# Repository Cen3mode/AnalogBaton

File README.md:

TO DO:
	redo GPIO layout,
	redo SD card slot,
	get rid of CAN bus connector (leave broken out on pins),
	redo power from charge pumps to LDOs where possible for simplicity,
	make the board smaller,
	get rid of the cristall (using internal oscillator),
	choose USB-C port with only single row of pins,
	add M3 mounting holes,
	reconfigure charger and fuel gauge,
	add QSPI flash,

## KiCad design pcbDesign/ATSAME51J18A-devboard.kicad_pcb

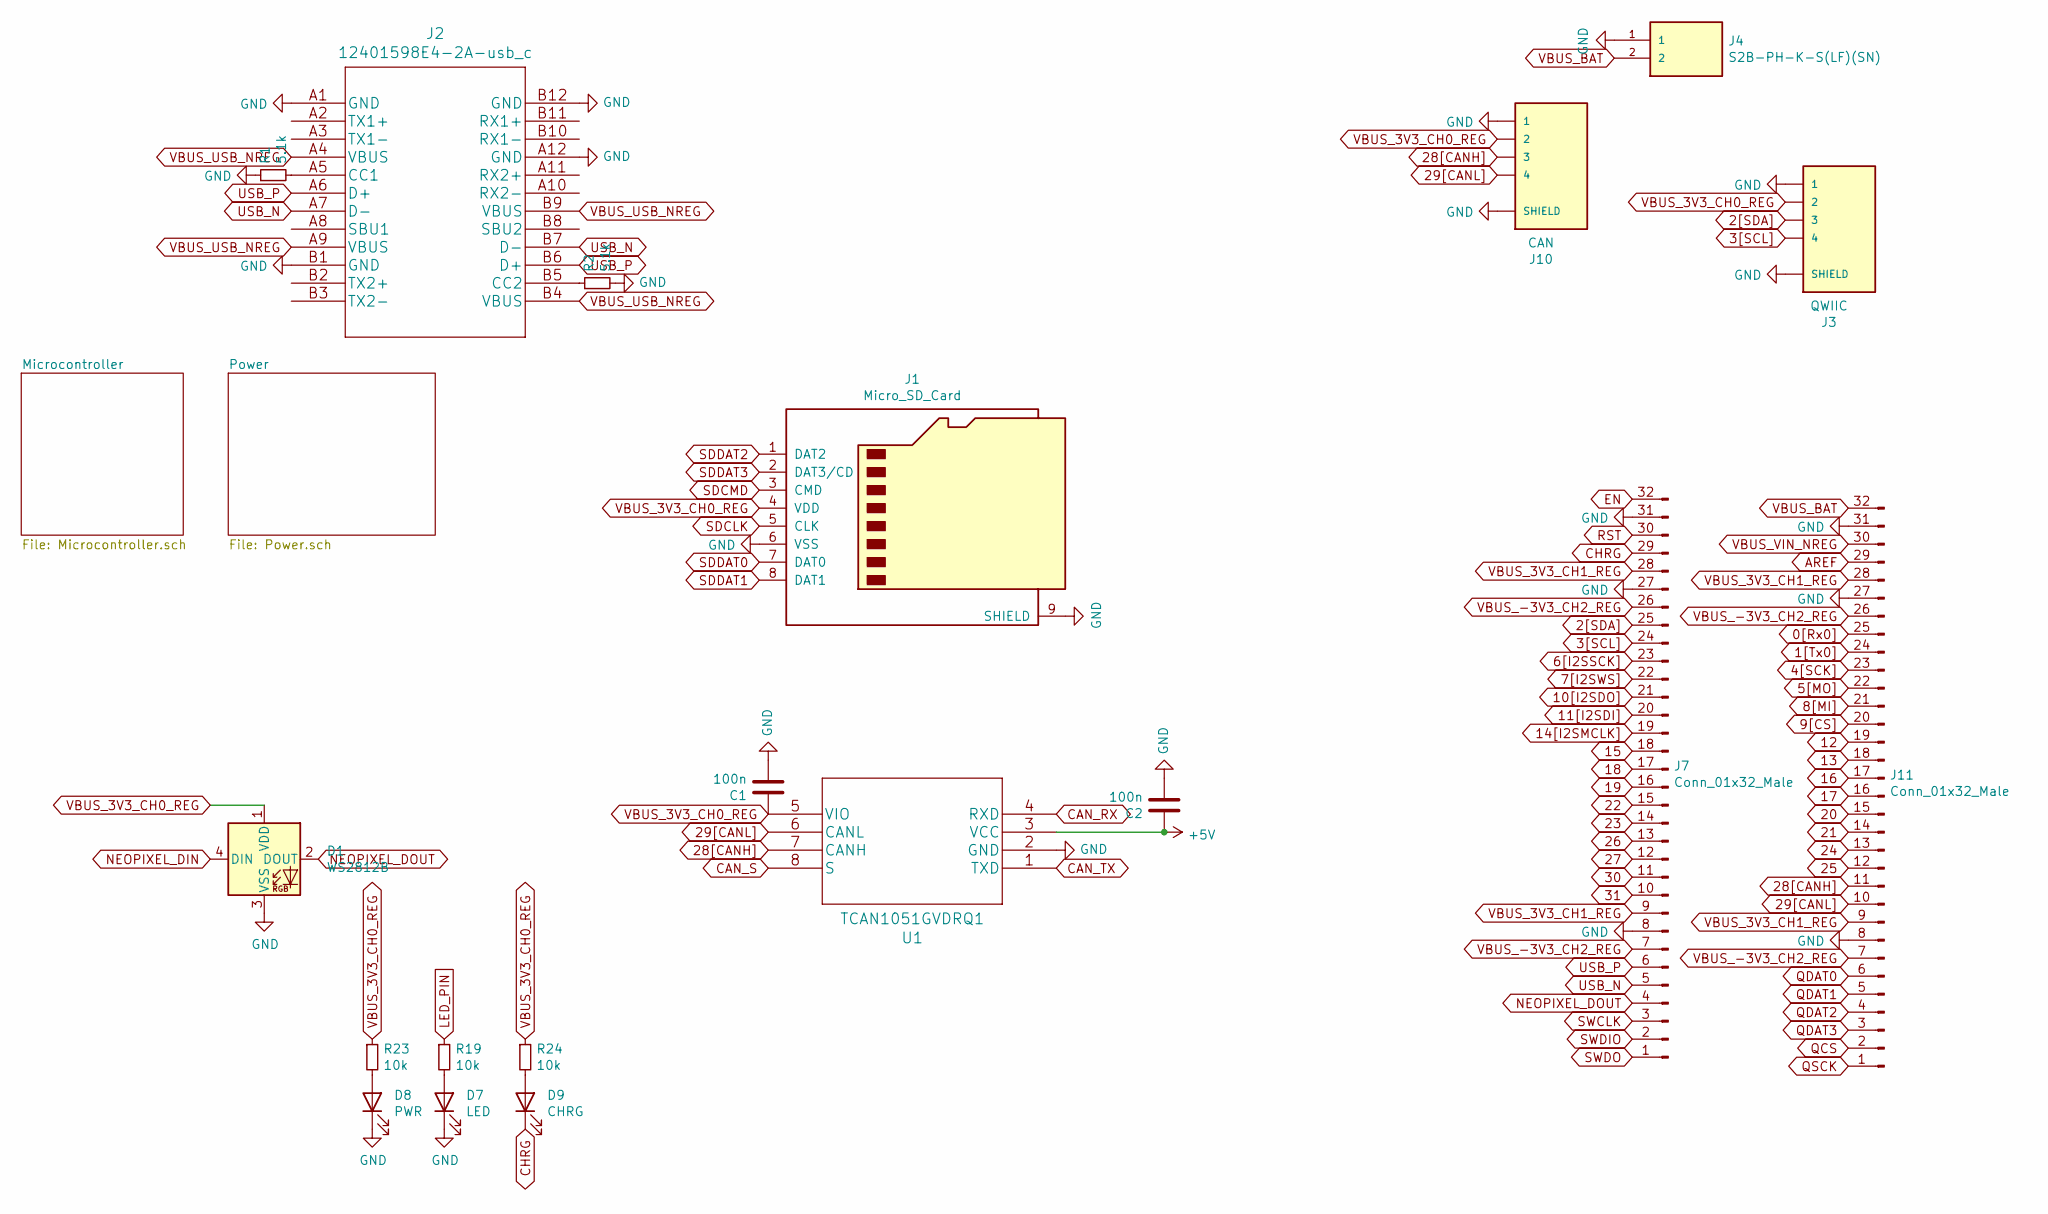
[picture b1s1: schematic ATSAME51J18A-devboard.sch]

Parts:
C1, C2: 100n; C_0402_1005Metric
D1: WS2812B; LED_WS2812B_PLCC4_5.0x5.0mm_P3.2mm
D7: LED; LED_0402_1005Metric
D8: PWR; LED_0402_1005Metric
D9: CHRG; LED_0402_1005Metric
J1: Micro_SD_Card; microSD_HC_Hirose_DM3D-SF
J2: 12401598E4-2A-usb_c; 12401598E4-2A
J3: QWIIC; JST_SM04B-SRSS-TB(LF)(SN)
J4: S2B-PH-K-S(LF)(SN); JST_S2B-PH-K-S(LF)(SN)
J7, J11: Conn_01x32_Male; PinSocket_1x32_P2.54mm_Vertical
J10: CAN; JST_SM04B-SRSS-TB(LF)(SN)
R1, R2: 5.1k; R_0402_1005Metric
R19, R23, R24: 10k; R_0402_1005Metric
U1: TCAN1051GVDRQ1

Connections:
0[Rx0]: J11.25; also elsewhere on the board
1[Tx0]: J11.24; also elsewhere on the board
2[SDA]: J3.3, J7.25; also elsewhere on the board
3[SCL]: J3.4, J7.24; also elsewhere on the board
4[SCK]: J1.5 (CLK), J11.23; also elsewhere on the board
5[MO]: J1.3 (CMD), J11.22; also elsewhere on the board
6[I2SSCK]: J7.23; also elsewhere on the board
7[I2SWS]: J7.22; also elsewhere on the board
8[MI]: J1.7 (DAT0), J11.21; also elsewhere on the board
9[CS]: J11.20; also elsewhere on the board
10[I2SDO]: J7.21; also elsewhere on the board
11[I2SDI]: J7.20; also elsewhere on the board
12: J11.19; also elsewhere on the board
13: J11.18, R19.1; also elsewhere on the board
14[I2SMCLK]: J7.19; also elsewhere on the board
15: J7.18; also elsewhere on the board
16: J11.17; also elsewhere on the board
17: J11.16; also elsewhere on the board
18: J7.17; also elsewhere on the board
19: J7.16; also elsewhere on the board
20: J11.15; also elsewhere on the board
21: J11.14; also elsewhere on the board
22: J7.15; also elsewhere on the board
23: J7.14; also elsewhere on the board
24: J11.13; also elsewhere on the board
25: J11.12; also elsewhere on the board
26: J7.13; also elsewhere on the board
27: J7.12; also elsewhere on the board
28[CANH]: J10.3, J11.11, U1.7 (CANH)
29[CANL]: J10.4, J11.10, U1.6 (CANL)
30: J7.11; also elsewhere on the board
31: J7.10; also elsewhere on the board
+5V: C2.2, U1.3 (VCC); also elsewhere on the board
AREF: J11.29; also elsewhere on the board
CAN_RX: U1.4 (RXD); also elsewhere on the board
CAN_S: U1.8 (S); also elsewhere on the board
CAN_TX: U1.1 (TXD); also elsewhere on the board
CHRG: D9.1 (K), J7.29; also elsewhere on the board
EN: J7.32; also elsewhere on the board
GND: C1.1, C2.1, D1.3 (VSS), D7.1 (K), D8.1 (K), J1.6 (VSS), J1.9 (SHIELD), J2.A1 (GND), J2.A12 (GND), J2.B1 (GND), J2.B12 (GND), J3.1, J3.S1 (SHIELD), J3.S2 (SHIELD), J4.1, J7.8, J7.27, J7.31, J10.1, J10.S1 (SHIELD), J10.S2 (SHIELD), J11.8, J11.27, J11.31, R1.1, R2.2, U1.2 (GND); also elsewhere on the board
NEOPIXEL_DIN: D1.4 (DIN); also elsewhere on the board
NEOPIXEL_DOUT: D1.2 (DOUT), J7.4
unnamed: D7.2 (A), R19.2
unnamed: D8.2 (A), R23.2
unnamed: D9.2 (A), R24.2
unnamed: J2.A5 (CC1), R1.2
unnamed: J2.B5 (CC2), R2.1
QCS: J11.2; also elsewhere on the board
QDAT0: J11.6; also elsewhere on the board
QDAT1: J11.5; also elsewhere on the board
QDAT2: J11.4; also elsewhere on the board
QDAT3: J11.3; also elsewhere on the board
QSCK: J11.1; also elsewhere on the board
RST: J7.30; also elsewhere on the board
SDDAT3: J1.2 (DAT3/CD); also elsewhere on the board
SWCLK: J7.3; also elsewhere on the board
SWDIO: J7.2; also elsewhere on the board
SWDO: J7.1; also elsewhere on the board
USB_N: J2.A7 (D-), J2.B7 (D-), J7.5; also elsewhere on the board
USB_P: J2.A6 (D+), J2.B6 (D+), J7.6; also elsewhere on the board
VBUS_3V3_CH0_REG: C1.2, D1.1 (VDD), J1.4 (VDD), J3.2, J10.2, R23.1, R24.1, U1.5 (VIO); also elsewhere on the board
VBUS_3V3_CH1_REG: J7.9, J7.28, J11.9, J11.28; also elsewhere on the board
VBUS_-3V3_CH2_REG: J7.7, J7.26, J11.7, J11.26; also elsewhere on the board
VBUS_BAT: J4.2, J11.32; also elsewhere on the board
VBUS_USB_NREG: J2.A4 (VBUS), J2.A9 (VBUS), J2.B4 (VBUS), J2.B9 (VBUS); also elsewhere on the board
VBUS_VIN_NREG: J11.30; also elsewhere on the board

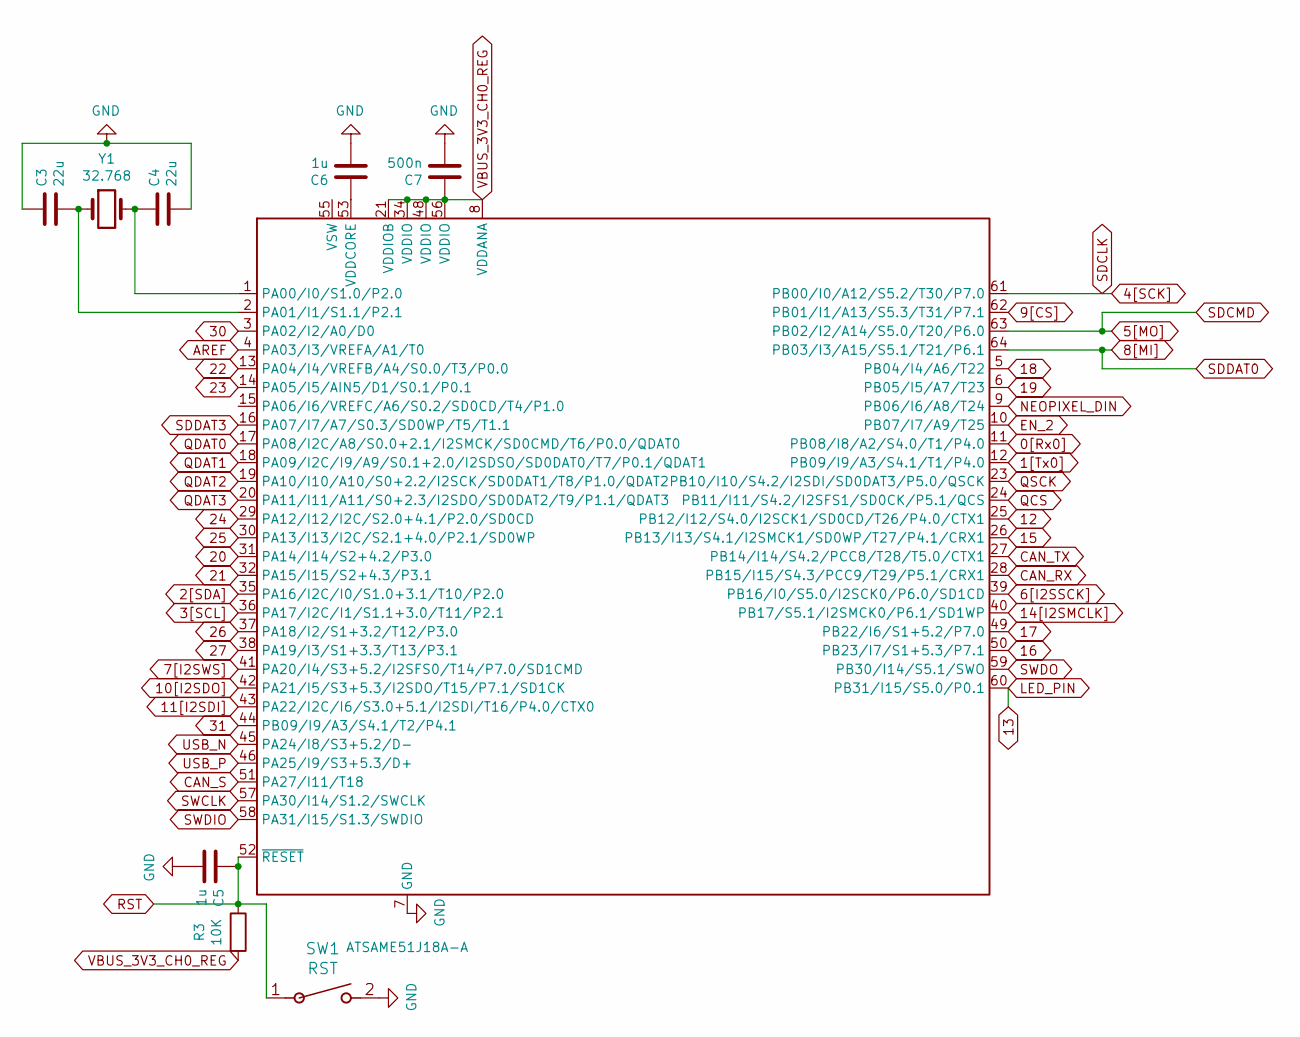
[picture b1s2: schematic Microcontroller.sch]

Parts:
C3, C4: 22u; C_0402_1005Metric
C5, C6: 1u; C_0402_1005Metric
C7: 500n; C_0402_1005Metric
R3: 10K; R_0402_1005Metric
SW1: RST; PTS636 SM25F SMTR LFS
U2: ATSAME51J18A-A; TQFP-64_10x10mm_P0.5mm
Y1: 32.768; Crystal_SMD_2012-2Pin_2.0x1.2mm

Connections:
0[Rx0]: U2.11 (PB08/I8/A2/S4.0/T1/P4.0); also elsewhere on the board
1[Tx0]: U2.12 (PB09/I9/A3/S4.1/T1/P4.0); also elsewhere on the board
2[SDA]: U2.35 (PA16/I2C/I0/S1.0+3.1/T10/P2.0); also elsewhere on the board
3[SCL]: U2.36 (PA17/I2C/I1/S1.1+3.0/T11/P2.1); also elsewhere on the board
4[SCK]: U2.61 (PB00/I0/A12/S5.2/T30/P7.0); also elsewhere on the board
5[MO]: U2.63 (PB02/I2/A14/S5.0/T20/P6.0); also elsewhere on the board
6[I2SSCK]: U2.39 (PB16/I0/S5.0/I2SCK0/P6.0/SD1CD); also elsewhere on the board
7[I2SWS]: U2.41 (PA20/I4/S3+5.2/I2SFS0/T14/P7.0/SD1CMD); also elsewhere on the board
8[MI]: U2.64 (PB03/I3/A15/S5.1/T21/P6.1); also elsewhere on the board
9[CS]: U2.62 (PB01/I1/A13/S5.3/T31/P7.1); also elsewhere on the board
10[I2SDO]: U2.42 (PA21/I5/S3+5.3/I2SDO/T15/P7.1/SD1CK); also elsewhere on the board
11[I2SDI]: U2.43 (PA22/I2C/I6/S3.0+5.1/I2SDI/T16/P4.0/CTX0); also elsewhere on the board
12: U2.25 (PB12/I12/S4.0/I2SCK1/SD0CD/T26/P4.0/CTX1); also elsewhere on the board
13: U2.60 (PB31/I15/S5.0/P0.1); also elsewhere on the board
14[I2SMCLK]: U2.40 (PB17/S5.1/I2SMCK0/P6.1/SD1WP); also elsewhere on the board
15: U2.26 (PB13/I13/S4.1/I2SMCK1/SD0WP/T27/P4.1/CR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); also elsewhere on the board
16: U2.50 (PB23/I7/S1+5.3/P7.1); also elsewhere on the board
17: U2.49 (PB22/I6/S1+5.2/P7.0); also elsewhere on the board
18: U2.5 (PB04/I4/A6/T22); also elsewhere on the board
19: U2.6 (PB05/I5/A7/T23); also elsewhere on the board
20: U2.31 (PA14/I14/S2+4.2/P3.0); also elsewhere on the board
21: U2.32 (PA15/I15/S2+4.3/P3.1); also elsewhere on the board
22: U2.13 (PA04/I4/VREFB/A4/S0.0/T3/P0.0); also elsewhere on the board
23: U2.14 (PA05/I5/AIN5/D1/S0.1/P0.1); also elsewhere on the board
24: U2.29 (PA12/I12/I2C/S2.0+4.1/P2.0/SD0CD); also elsewhere on the board
25: U2.30 (PA13/I13/I2C/S2.1+4.0/P2.1/SD0WP); also elsewhere on the board
26: U2.37 (PA18/I2/S1+3.2/T12/P3.0); also elsewhere on the board
27: U2.38 (PA19/I3/S1+3.3/T13/P3.1); also elsewhere on the board
30: U2.3 (PA02/I2/A0/D0); also elsewhere on the board
31: U2.44 (PB09/I9/A3/S4.1/T2/P4.1); also elsewhere on the board
AREF: U2.4 (PA03/I3/VREFA/A1/T0); also elsewhere on the board
CAN_RX: U2.28 (PB15/I15/S4.3/PCC9/T29/P5.1/CRX1); also elsewhere on the board
CAN_S: U2.51 (PA27/I11/T18); also elsewhere on the board
CAN_TX: U2.27 (PB14/I14/S4.2/PCC8/T28/T5.0/CTX1); also elsewhere on the board
EN_2: U2.10 (PB07/I7/A9/T25); also elsewhere on the board
GND: C3.2, C4.1, C5.1, C6.1, C7.1, SW1.2, U2.7 (GND), U2.22 (GND), U2.33 (GND), U2.47 (GND), U2.54 (GND); also elsewhere on the board
NEOPIXEL_DIN: U2.9 (PB06/I6/A8/T24); also elsewhere on the board
unnamed: C3.1, U2.2 (PA01/I1/S1.1/P2.1), Y1.1
unnamed: C4.2, U2.1 (PA00/I0/S1.0/P2.0), Y1.2
unnamed: C6.2, U2.53 (VDDCORE)
QCS: U2.24 (PB11/I11/S4.2/I2SFS1/SD0CK/P5.1/QCS); also elsewhere on the board
QDAT0: U2.17 (PA08/I2C/A8/S0.0+2.1/I2SMCK/SD0CMD/T6/P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); also elsewhere on the board
QDAT1: U2.18 (PA09/I2C/I9/A9/S0.1+2.0/I2SDSO/SD0DAT0/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); also elsewhere on the board
QDAT2: U2.19 (PA10/I10/A10/S0+2.2/I2SCK/SD0DAT1/T8/P1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); also elsewhere on the board
QDAT3: U2.20 (PA11/I11/A11/S0+2.3/I2SDO/SD0DAT2/T9/P1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); also elsewhere on the board
QSCK: U2.23 (PB10/I10/S4.2/I2SDI/SD0DAT3/P5.0/QSCK); also elsewhere on the board
RST: C5.2, R3.1, SW1.1, U2.52 (~RESET); also elsewhere on the board
SDDAT3: U2.16 (PA07/I7/A7/S0.3/SD0WP/T5/T1.1); also elsewhere on the board
SWCLK: U2.57 (PA30/I14/S1.2/SWCLK); also elsewhere on the board
SWDIO: U2.58 (PA31/I15/S1.3/SWDIO); also elsewhere on the board
SWDO: U2.59 (PB30/I14/S5.1/SWO); also elsewhere on the board
USB_N: U2.45 (PA24/I8/S3+5.2/D-); also elsewhere on the board
USB_P: U2.46 (PA25/I9/S3+5.3/D+); also elsewhere on the board
VBUS_3V3_CH0_REG: C7.2, R3.2, U2.8 (VDDANA), U2.21 (VDDIOB), U2.34 (VDDIO), U2.48 (VDDIO), U2.56 (VDDIO); also elsewhere on the board

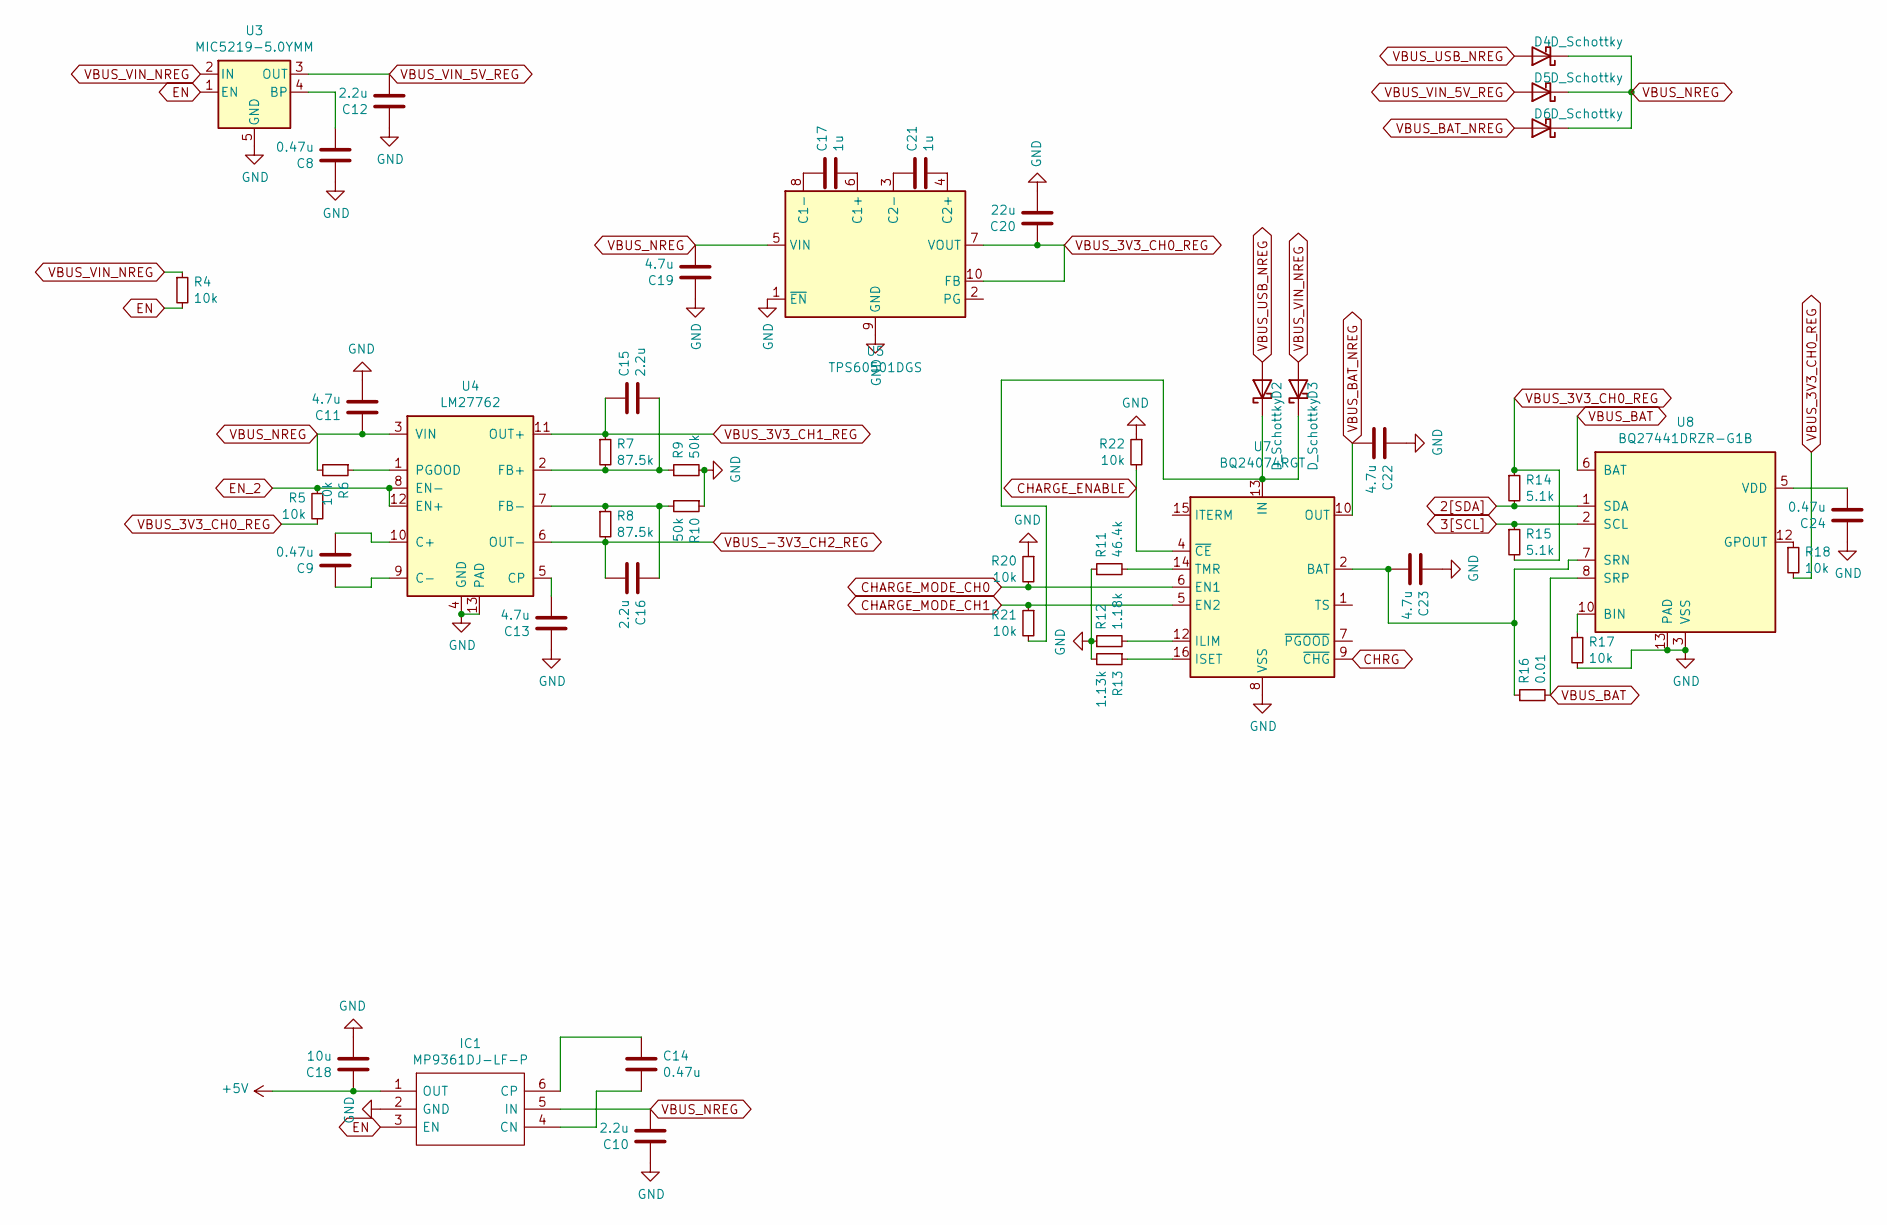
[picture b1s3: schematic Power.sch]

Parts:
C8, C9, C14, C24: 0.47u; C_0402_1005Metric
C10, C12, C15, C16: 2.2u; C_0402_1005Metric
C11, C13, C19, C22, C23: 4.7u; C_0402_1005Metric
C17, C21: 1u; C_0402_1005Metric
C18: 10u; C_0402_1005Metric
C20: 22u; C_0402_1005Metric
D2, D3, D4, D5, D6: D_Schottky; D_0402_1005Metric
IC1: MP9361DJ-LF-P; SOT95P280X100-6N; Mouser Part Number 946-MP9361DJLFP
R4, R5, R6, R17, R18, R20, R21, R22: 10k; R_0402_1005Metric
R7, R8: 87.5k; R_0402_1005Metric
R9, R10: 50k; R_0402_1005Metric
R11: 46.4k; R_0402_1005Metric
R12: 1.18k; R_0402_1005Metric
R13: 1.13k; R_0402_1005Metric
R14, R15: 5.1k; R_0402_1005Metric
R16: 0.01; R_0402_1005Metric
U3: MIC5219-5.0YMM; MSOP-8_3x3mm_P0.65mm
U4: LM27762; WSON-12-1EP_3x2mm_P0.5mm_EP1x2.65_ThermalVias
U5: TPS60501DGS; MSOP-10_3x3mm_P0.5mm
U7: BQ24074RGT; VQFN-16-1EP_3x3mm_P0.5mm_EP1.6x1.6mm
U8: BQ27441DRZR-G1B; Texas_S-PDSO-N12

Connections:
2[SDA]: R14.2, U8.1 (SDA); also elsewhere on the board
3[SCL]: R15.1, U8.2 (SCL); also elsewhere on the board
+5V: C18.2, IC1.1 (OUT); also elsewhere on the board
CHARGE_ENABLE: R22.2, U7.4 (~CE)
CHARGE_MODE_CH0: R20.2, U7.6 (EN1)
CHARGE_MODE_CH1: R21.1, U7.5 (EN2)
CHRG: U7.9 (~CHG); also elsewhere on the board
EN: IC1.3 (EN), R4.2, U3.1 (EN); also elsewhere on the board
EN_2: R5.1, U4.8 (EN-), U4.12 (EN+); also elsewhere on the board
GND: C8.2, C10.2, C11.1, C12.2, C13.2, C18.1, C19.2, C20.1, C22.2, C23.2, C24.2, IC1.2 (GND), R9.2, R10.1, R11.1, R12.1, R13.2, R17.2, R20.1, R22.1, U3.5 (GND), U3.6 (GND), U3.7 (GND), U3.8 (GND), U4.4 (GND), U4.13 (PAD), U5.1 (~EN), U5.9 (GND), U7.8 (VSS), U7.17 (VSS), U8.3 (VSS), U8.13 (PAD); also elsewhere on the board
unnamed: C8.1, U3.4 (BP)
unnamed: C9.1, U4.10 (C+)
unnamed: C9.2, U4.9 (C-)
unnamed: C13.1, U4.5 (CP)
unnamed: C14.1, IC1.4 (CN)
unnamed: C14.2, IC1.6 (CP)
unnamed: C15.1, R7.2, R9.1, U4.2 (FB+)
unnamed: C16.2, R8.1, R10.2, U4.7 (FB-)
unnamed: C17.1, U5.6 (C1+)
unnamed: C17.2, U5.8 (C1-)
unnamed: C21.1, U5.4 (C2+)
unnamed: C21.2, U5.3 (C2-)
unnamed: C23.1, R16.1, U7.2 (BAT), U7.3 (BAT), U8.7 (SRN)
unnamed: C24.1, U8.5 (VDD)
unnamed: D2.1 (K), D3.1 (K), R21.2, U7.13 (IN)
unnamed: R6.1, U4.1 (PGOOD)
unnamed: R11.2, U7.14 (TMR)
unnamed: R12.2, U7.12 (ILIM)
unnamed: R13.1, U7.16 (ISET)
unnamed: R17.1, U8.10 (BIN)
unnamed: R18.1, U8.12 (GPOUT)
VBUS_3V3_CH0_REG: C20.2, R5.2, R14.1, R15.2, R18.2, U5.7 (VOUT), U5.10 (FB); also elsewhere on the board
VBUS_3V3_CH1_REG: C15.2, R7.1, U4.11 (OUT+); also elsewhere on the board
VBUS_-3V3_CH2_REG: C16.1, R8.2, U4.6 (OUT-); also elsewhere on the board
VBUS_BAT: R16.2, U8.6 (BAT), U8.8 (SRP); also elsewhere on the board
VBUS_BAT_NREG: C22.1, D6.2 (A), U7.10 (OUT), U7.11 (OUT)
VBUS_NREG: C10.1, C11.2, C19.1, D4.1 (K), D5.1 (K), D6.1 (K), IC1.5 (IN), R6.2, U4.3 (VIN), U5.5 (VIN)
VBUS_USB_NREG: D2.2 (A), D4.2 (A); also elsewhere on the board
VBUS_VIN_5V_REG: C12.1, D5.2 (A), U3.3 (OUT)
VBUS_VIN_NREG: D3.2 (A), R4.1, U3.2 (IN); also elsewhere on the board

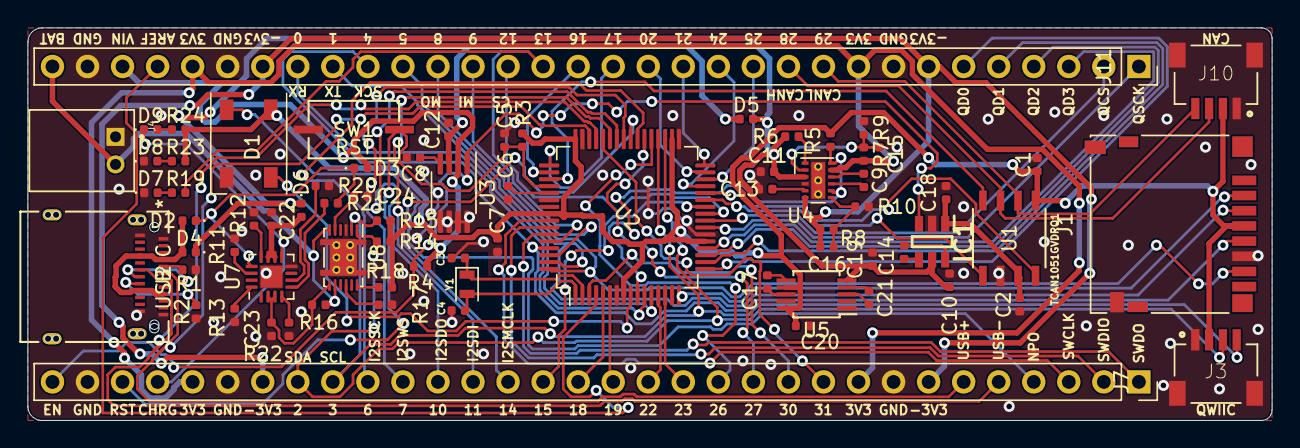
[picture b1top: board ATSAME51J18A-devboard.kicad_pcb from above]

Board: 2 copper layers, 90.2 x 28.4 mm, 74 parts (0 on the bottom side), 97 nets.

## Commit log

2021-03-03 Added forum discussion
2021-03-03 Moved cicruit designes to the repo
2021-03-03 Configured battery gas gauge
2021-03-05 Finished schematic v0.1
2021-03-05 Cerrected errors in the schematic and began work on the pcb layout
2021-03-06 Fixed power rail enabling systems and rearanged pins for easier use
2021-03-07 Changed pin pitch to 2.54mm
2021-03-10 Finnished routing
2021-03-10 Panelized the design
2021-03-11 Labeled pins done
2021-03-11 Repanelized board after adding pin descriptions
2021-03-12 Changed the layout of pins to make room for SWD and made the board longer
2021-03-13 Corrected pin header spacing to fit on a bread board
2021-03-13 Panelized the final design
2021-03-14 Reconfigured charging circuit
2021-03-14 Generated bom file
2021-03-15 Rewired SD card to SPI for ease of use
2021-03-16 Started routing manually
2021-03-17 Contnueing routing
2021-03-18 Finnished routing for the prototype(v0.1)
2021-03-18 Panelized the prototype(v0.1)
2021-03-18 Fixed panelizing issues
2021-03-19 Swapped components for more avaiable ones
2021-03-19 Generated new BOM file
2021-03-19 Panelized
2021-03-19 Added logo
2021-03-19 Panelized with logo
2021-03-19 Finnished final BOM file
2021-03-20 Fixed some DRC errors
2021-03-21 Fabrication files
2021-03-22 Finnished routing board prototype(v0.2)
2021-03-22 Panelised prototype(v0.2)
2021-03-22 Generated gerber files for prototype(v0.2)
2021-04-16 Some arduino configs
2021-04-19 Begun to make changes to the design
2021-04-19 Added to do list
2021-04-19 Reformated README.md

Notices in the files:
parts and their libraries:
Copyright 2016 Accelerated Designs. All rights reserved.
